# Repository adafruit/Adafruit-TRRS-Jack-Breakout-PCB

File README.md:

## Adafruit TRRS Jack Breakout PCB

<a href="http://www.adafruit.com/products/5764"><br/>
Click here to purchase one from the Adafruit shop</a>

PCB files for the Adafruit TRRS Jack Breakout. 

Format is EagleCAD schematic and board layout
* https://www.adafruit.com/product/5764

### Description

Tip-Ring-Ring-Sleeve style audio cables are often used for situations where you want stereo audio and then an extra contact for a microphone input. For example, headsets for cell phones. Also called TRRS jacks for short, they're also handy if you happen to want to use common audio cables for low-speed data transmission with power, ground and two data lines.

This breakout board is simple but has everything you need to interface with TRRS cables: not only do you get the four contacts but also two switched outputs:

* When the jack is not inserted, the left switch is connected to the left contact and the right switch to the right contact.
* When the jack is inserted, the left and right switch pins 'float'. You can use these switches to auto-switch from a built in speaker to headphone when plugged in, or to detect when headphone is not inserted to power down or mute.

We like this jack in particular because it has two through-hole contacts near the opening for a good mechanical connection. Comes fully assembled on a breakout board with mounting holes and lil bit of header in case you want to use it with a breadboard.

### License

Adafruit invests time and resources providing this open source design, please support Adafruit and open-source hardware by purchasing products from [Adafruit](https://www.adafruit.com)!

Designed by Limor Fried/Ladyada for Adafruit Industries.

Creative Commons Attribution/Share-Alike, all text above must be included in any redistribution. 
See license.txt for additional details.

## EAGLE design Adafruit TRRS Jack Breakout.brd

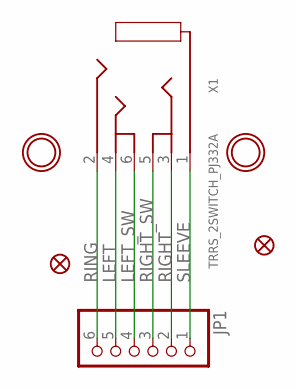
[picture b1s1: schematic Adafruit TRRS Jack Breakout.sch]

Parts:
FID1, FID2: FIDUCIAL_1MM
JP1: HEADER-1X670MIL; 1X06_ROUND_70
U$2, U$4: MOUNTINGHOLE2.0; MOUNTINGHOLE_2.0_PLATED
X1: TRRS_2SWITCH_PJ332A; PJ-332A

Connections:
LEFT: JP1.5, X1.4 (TIP)
LEFT_SW: JP1.4, X1.6 (TIP_SW)
RIGHT: JP1.2, X1.3 (RING2)
RIGHT_SW: JP1.3, X1.5 (R2_SW)
RING: JP1.6, X1.2 (RING1)
SLEEVE: JP1.1, X1.1 (RING)

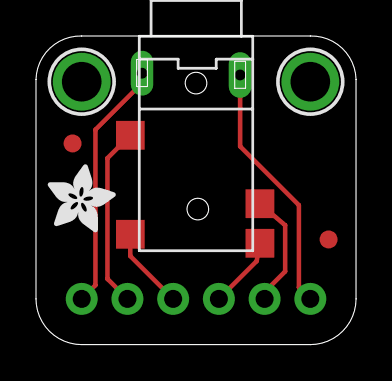
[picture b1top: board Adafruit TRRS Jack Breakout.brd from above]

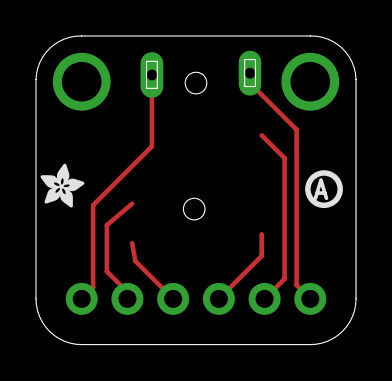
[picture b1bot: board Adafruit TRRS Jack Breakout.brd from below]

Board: 2 copper layers, 17.8 x 17.1 mm, 19 parts (3 on the bottom side), 6 nets.

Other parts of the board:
PLABEL0: PLABEL0
PLABEL1: PLABEL1
PLABEL2: PLABEL2
PLABEL3: PLABEL3
PLABEL4: PLABEL4
PLABEL5: PLABEL5
PLABEL6: PLABEL6
PLABEL7: PLABEL7
PLABEL8: PLABEL8
PLABEL9: PLABEL9
U$1: PCBFEAT-REV-040
U$3: ADAFRUIT_2.5MM
U$5: ADAFRUIT_3.5MM

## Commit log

2023-06-13 Add board files.

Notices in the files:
parts and their libraries:
microbuilder: This work is placed in the public domain, and may be freely used for commercial and non-commercial work with the following conditions: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
